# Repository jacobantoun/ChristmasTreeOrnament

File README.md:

# Christmas Tree Ornament
I made these Christmas tree ornaments for friends and coworkers. KiCad PCB files and Source Code included.

Right now all the ornament does is flash the lights in a line, then a defined pattern. Nothing special.

LEDs are hooked up to PA0-7 and PB0.

The code is pretty self explanitory with the comments in there.

ATTiny44A:
https://www.digikey.com/product-detail/en/microchip-technology/ATTINY44A-PU/ATTINY44A-PU-ND/1914707

200 Ohm Resistor:
https://www.digikey.com/product-detail/en/stackpole-electronics-inc/CF18JT200R/CF18JT200RCT-ND/2022725

CR2032:
https://www.digikey.com/product-detail/en/panasonic-bsg/CR2032/P189-ND/31939

Gold LEDs:
https://www.amazon.com/gp/product/B077XBLKQR/ref=ppx_yo_dt_b_search_asin_title?ie=UTF8&psc=1

Red LEDs:
https://www.amazon.com/gp/product/B077X96JVG/ref=ppx_yo_dt_b_search_asin_title?ie=UTF8&psc=1

Green LEDs:
https://www.amazon.com/gp/product/B077XB9CWH/ref=ppx_yo_dt_b_search_asin_title?ie=UTF8&psc=1

Battery Holder:
https://www.digikey.com/product-detail/en/linx-technologies-inc/BAT-HLD-001-THM/BAT-HLD-001-THM-ND/3044009

I used 1 gold LED on the top of the tree, and the rest green and red alternating across the tree. 

Future design improvements:

Adding a small power switch! Currently you have to remove the battery or wedge a piece of card stock between the battery holder and battery to turn it off.

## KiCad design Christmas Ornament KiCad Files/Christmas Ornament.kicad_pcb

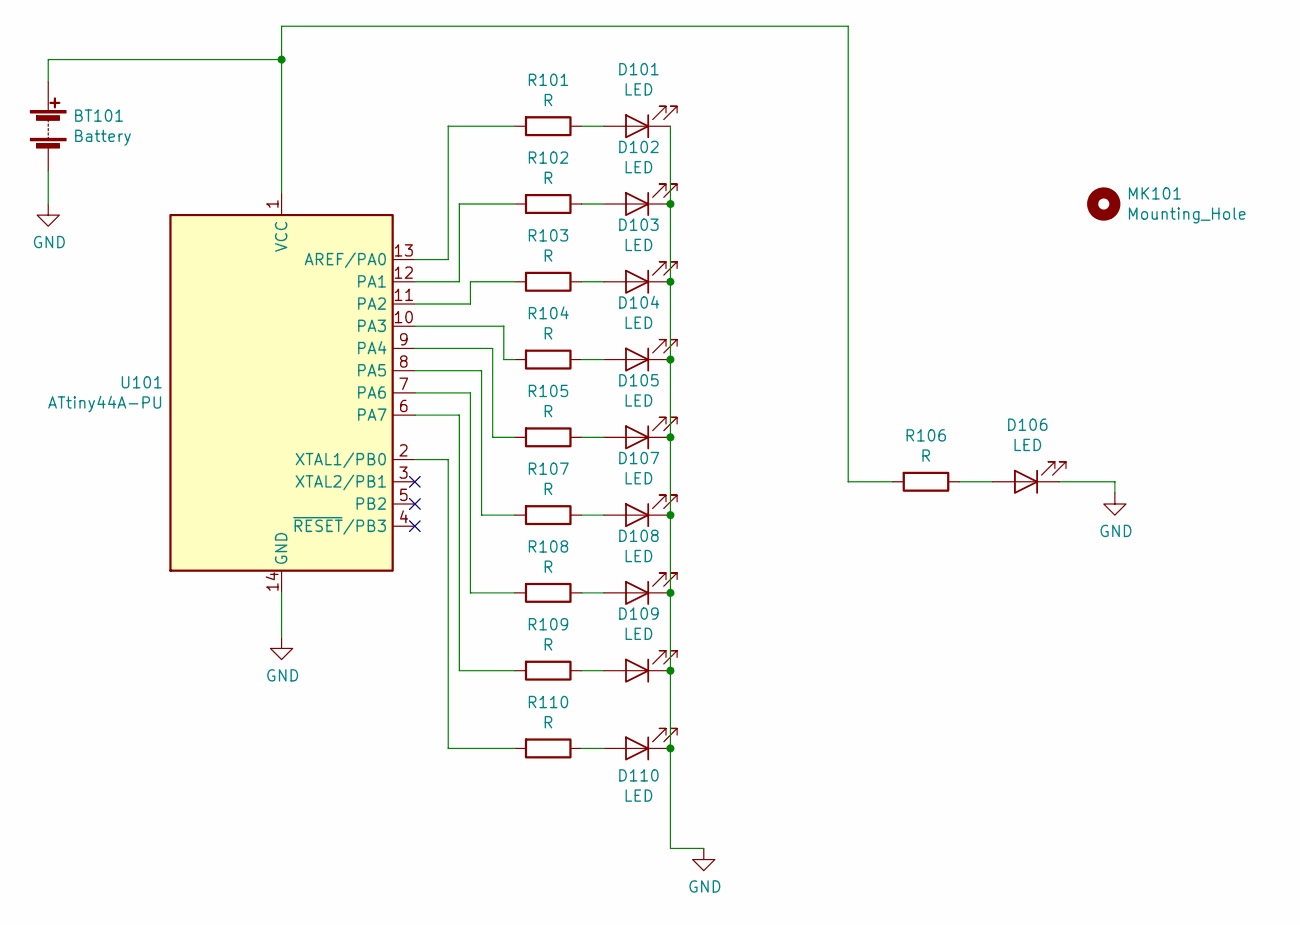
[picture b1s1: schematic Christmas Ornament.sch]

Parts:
BT101: Battery; 2032_Battery_Holder
D101, D102, D103, D104, D105, D106, D107, D108, D109, D110: LED; LED_D3.0mm
MK101: Mounting_Hole; TinyHoleforHook
R101, R102, R103, R104, R105, R106, R107, R108, R109, R110: R; R_Axial_DIN0204_L3.6mm_D1.6mm_P5.08mm_Horizontal
U101: ATtiny44A-PU; DIP-14_W7.62mm_LongPads

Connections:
GND: BT101.2 (-), D101.1 (K), D102.1 (K), D103.1 (K), D104.1 (K), D105.1 (K), D106.1 (K), D107.1 (K), D108.1 (K), D109.1 (K), D110.1 (K), U101.14 (GND)
unnamed: BT101.1 (+), R106.2, U101.1 (VCC)
unnamed: D101.2 (A), R101.1
unnamed: D102.2 (A), R102.1
unnamed: D103.2 (A), R103.1
unnamed: D104.2 (A), R104.1
unnamed: D105.2 (A), R105.1
unnamed: D106.2 (A), R106.1
unnamed: D107.2 (A), R107.1
unnamed: D108.2 (A), R108.1
unnamed: D109.2 (A), R109.1
unnamed: D110.2 (A), R110.1
unnamed: R101.2, U101.13 (AREF/PA0)
unnamed: R102.2, U101.12 (PA1)
unnamed: R103.2, U101.11 (PA2)
unnamed: R104.2, U101.10 (PA3)
unnamed: R105.2, U101.9 (PA4)
unnamed: R107.2, U101.8 (PA5)
unnamed: R108.2, U101.7 (PA6)
unnamed: R109.2, U101.6 (PA7)
unnamed: R110.2, U101.2 (XTAL1/PB0)

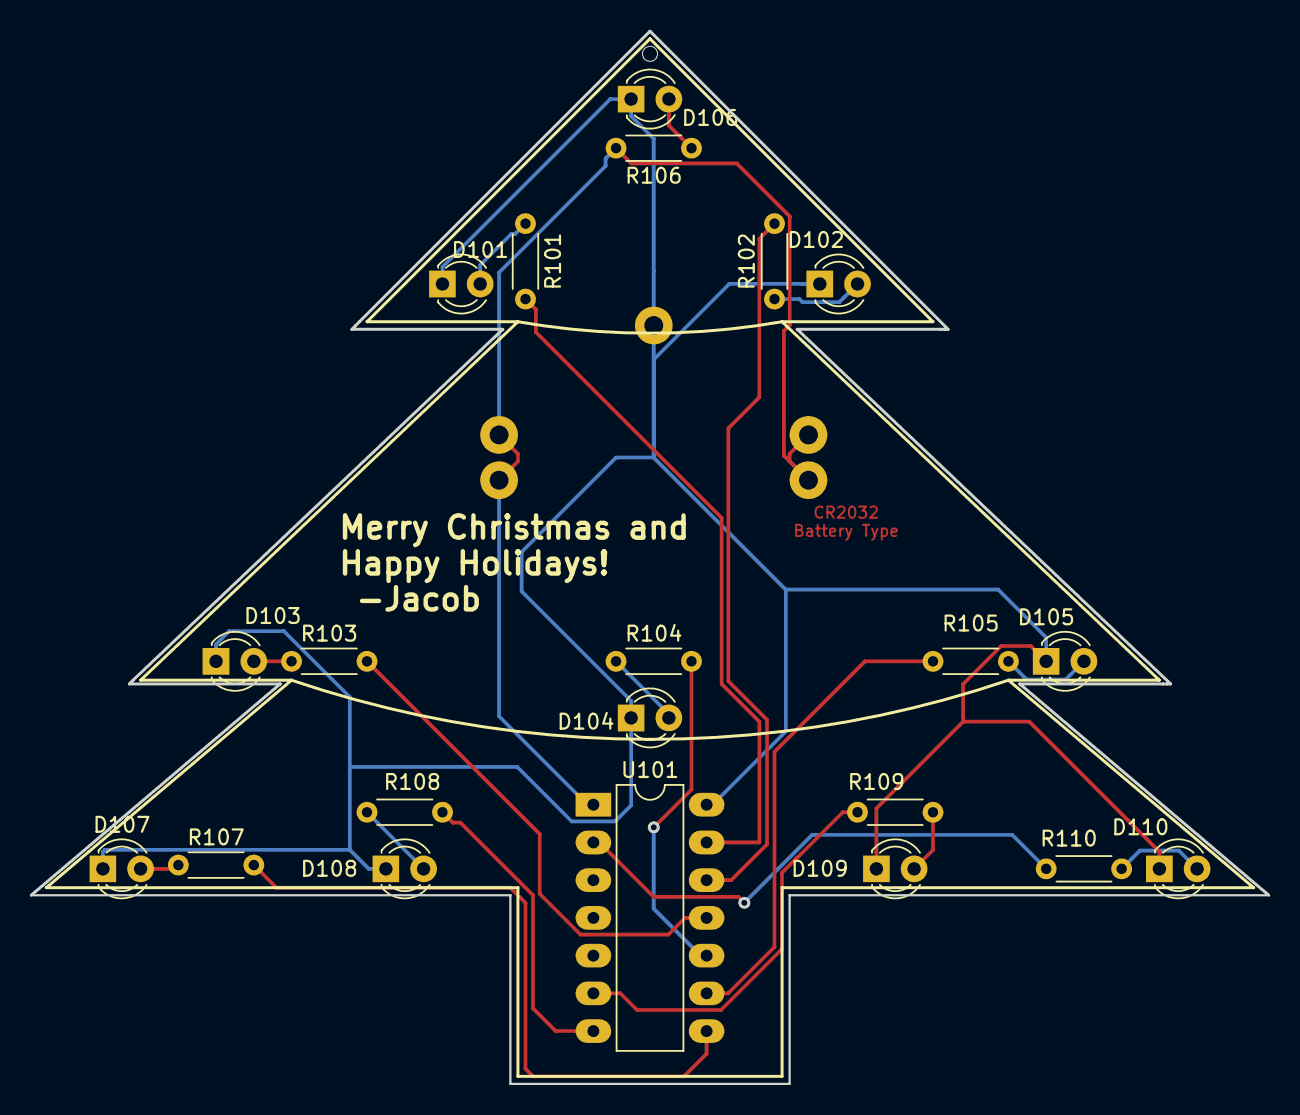
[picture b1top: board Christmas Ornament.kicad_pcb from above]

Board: 2 copper layers, 83.3 x 70.8 mm, 23 parts (1 on the bottom side), 21 nets.

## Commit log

2019-08-15 Create test
